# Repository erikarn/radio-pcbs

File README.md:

# Welcome!

This is Adrian's playpen for learning and building little radio PCB projects.

All of these projects are licenced under CC BY-SA 2.0 (https://creativecommons.org/licenses/by-sa/2.0/).
Please contact me if you have any commercial desires but don't wish to
share your designs.

Thanks!

-Adrian Chadd
(KK6VQK)

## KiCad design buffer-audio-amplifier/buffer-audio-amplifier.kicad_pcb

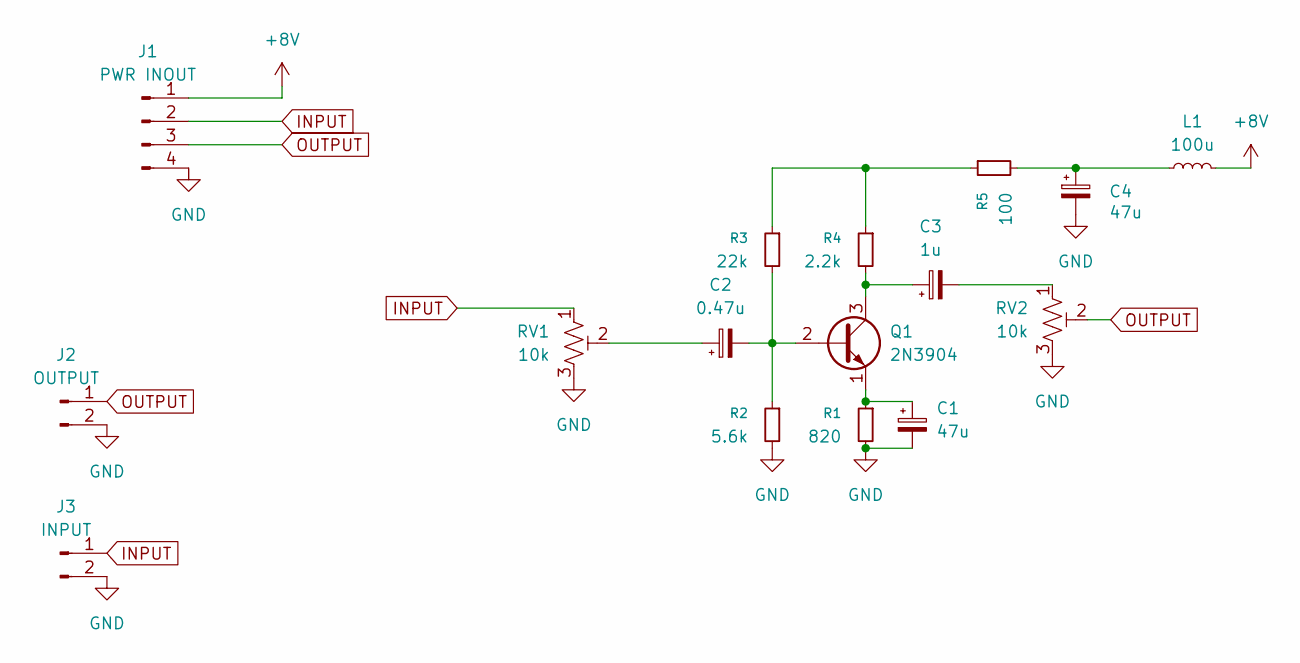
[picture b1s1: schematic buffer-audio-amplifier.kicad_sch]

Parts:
C1, C4: 47u; CP_Radial_D6.3mm_P2.50mm
C2: 0.47u; CP_Radial_D6.3mm_P2.50mm
C3: 1u; CP_Radial_D6.3mm_P2.50mm
J1: PWR INOUT; PinHeader_1x04_P2.54mm_Vertical
J2: OUTPUT; PinHeader_1x02_P2.54mm_Vertical
J3: INPUT; PinHeader_1x02_P2.54mm_Vertical
L1: 100u; L_Axial_L5.3mm_D2.2mm_P7.62mm_Horizontal_Vishay_IM-1
Q1: 2N3904; TO-92_Inline
R1: 820; R_Axial_DIN0204_L3.6mm_D1.6mm_P5.08mm_Horizontal
R2: 5.6k; R_Axial_DIN0204_L3.6mm_D1.6mm_P5.08mm_Horizontal
R3: 22k; R_Axial_DIN0204_L3.6mm_D1.6mm_P5.08mm_Horizontal
R4: 2.2k; R_Axial_DIN0204_L3.6mm_D1.6mm_P5.08mm_Horizontal
R5: 100; R_Axial_DIN0207_L6.3mm_D2.5mm_P7.62mm_Horizontal
RV1, RV2: 10k; Potentiometer_Piher_PT-10-V05_Vertical

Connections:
+8V: J1.1, L1.2
GND: C1.2, C4.2, J1.4, J2.2, J3.2, R1.2, R2.2, RV1.3, RV2.3
INPUT: J1.2, J3.1, RV1.1
unnamed: C2.1, RV1.2
unnamed: C3.2, RV2.1
unnamed: C4.1, L1.1, R5.2
unnamed: C2.2, Q1.2 (B), R2.1, R3.2
unnamed: C3.1, Q1.3 (C), R4.2
unnamed: C1.1, Q1.1 (E), R1.1
unnamed: R3.1, R4.1, R5.1
OUTPUT: J1.3, J2.1, RV2.2

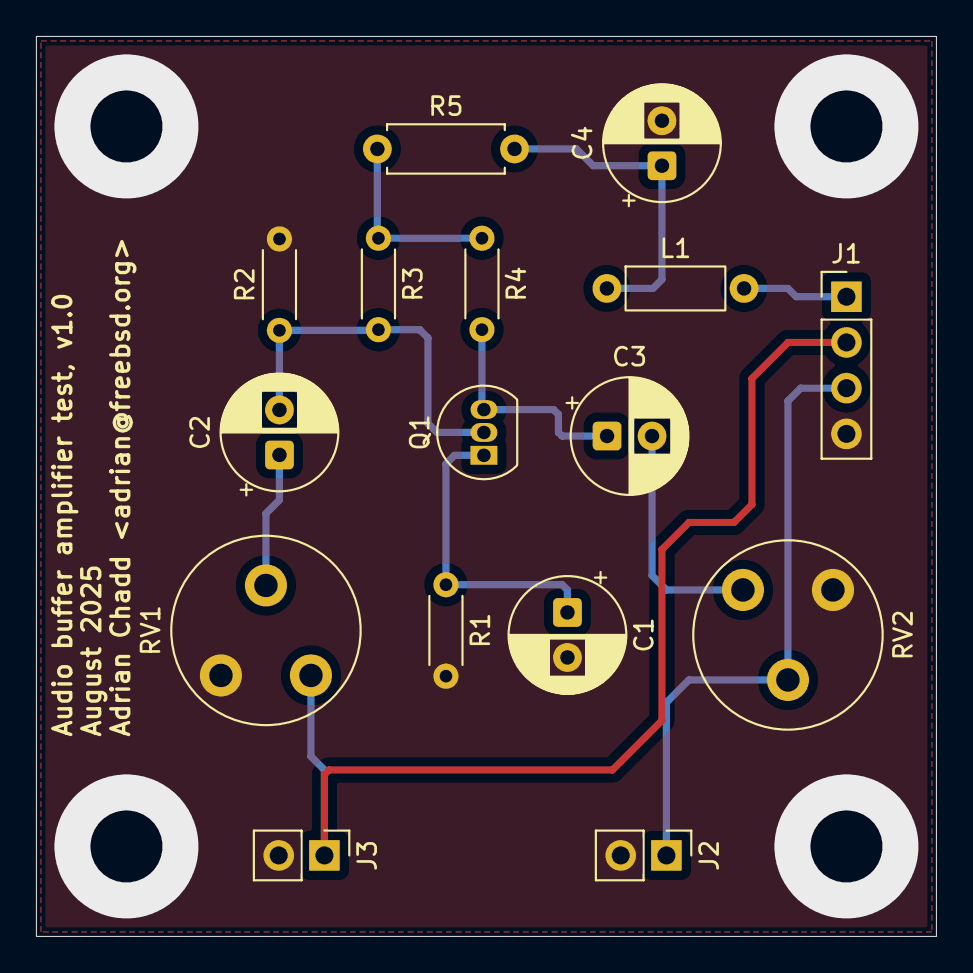
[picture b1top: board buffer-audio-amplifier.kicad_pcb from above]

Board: 2 copper layers, 50.0 x 50.0 mm, 16 parts (0 on the bottom side), 11 nets.

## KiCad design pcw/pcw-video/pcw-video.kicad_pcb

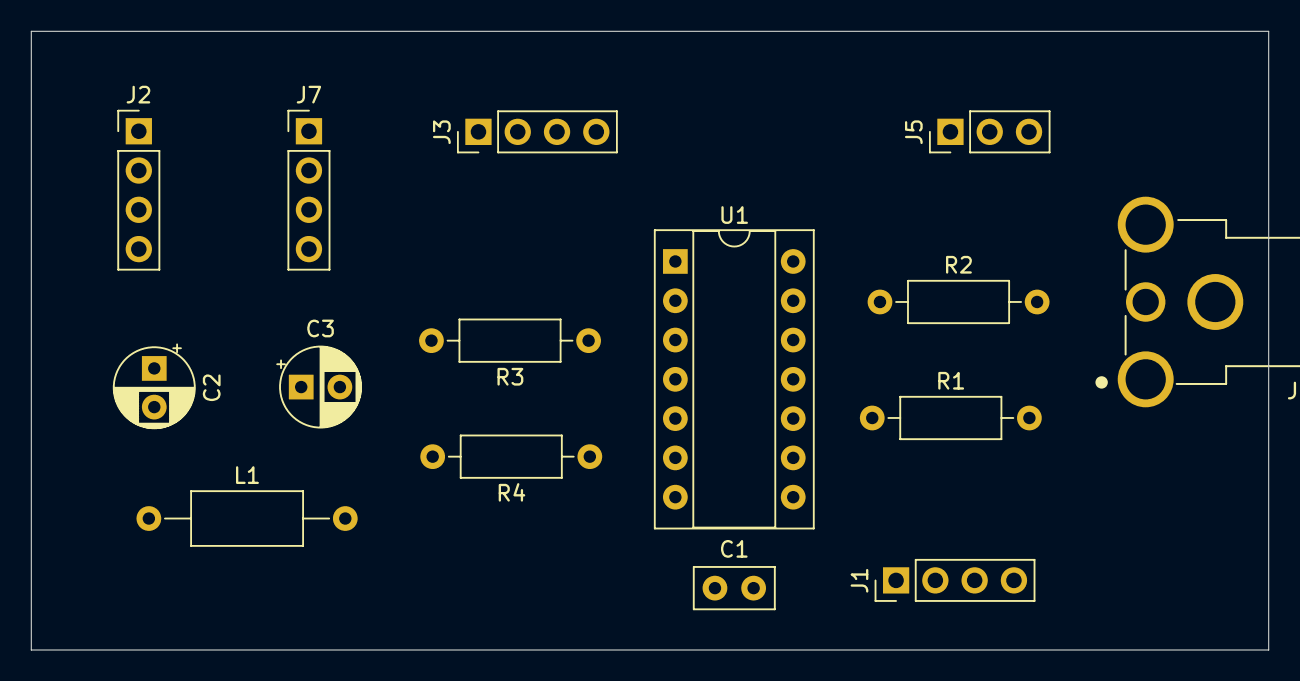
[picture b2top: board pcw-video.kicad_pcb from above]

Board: 2 copper layers, 80.0 x 40.0 mm, 15 parts (0 on the bottom side), 13 nets, no tracks yet.

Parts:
C1: 0.1uF; C_Disc_D5.0mm_W2.5mm_P2.50mm
C2, C3: 1uF; CP_Radial_D5.0mm_P2.50mm
J1: video in; PinHeader_1x04_P2.54mm_Vertical
J2: keyboard in; PinHeader_1x04_P2.54mm_Vertical
J3: video out; PinHeader_1x04_P2.54mm_Vertical
J4: composite out; CUI_RCJ-017
J5: video config; PinHeader_1x03_P2.54mm_Vertical
J7: keyboard out; PinHeader_1x04_P2.54mm_Vertical
L1: 100uH; L_Axial_L7.0mm_D3.3mm_P12.70mm_Horizontal_Fastron_MICC
R1, R2: 5.6k; R_Axial_DIN0207_L6.3mm_D2.5mm_P10.16mm_Horizontal
R3: 470; R_Axial_DIN0207_L6.3mm_D2.5mm_P10.16mm_Horizontal
R4: 1k; R_Axial_DIN0207_L6.3mm_D2.5mm_P10.16mm_Horizontal
U1: 74HC00; CERDIP-14_W7.62mm_SideBrazed_Socket

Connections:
5V_IN: C2.1, J2.2, L1.1
+5V: C1.1, C3.1, J5.1, J7.2, L1.2, U1.2, U1.5, U1.9, U1.12, U1.14 (VCC)
COMP: R3.2, R4.2
GND: C1.2, C2.2, C3.2, J1.2, J1.4, J2.1, J3.2, J3.4, J4.2 (Ext), J5.3, J7.1, R2.2, U1.7 (GND)
unnamed: U1.1, U1.11
unnamed: U1.4, U1.8
PCW_CLK: J2.4, J7.4
PCW_DAT: J2.3, J7.3
SEL1: J5.2, R1.2
SIN: J1.1, R1.1, U1.10
SOUT: J3.1, R4.1, U1.6
VIN: J1.3, R2.1, U1.13
VOUT: J3.3, R3.1, U1.3

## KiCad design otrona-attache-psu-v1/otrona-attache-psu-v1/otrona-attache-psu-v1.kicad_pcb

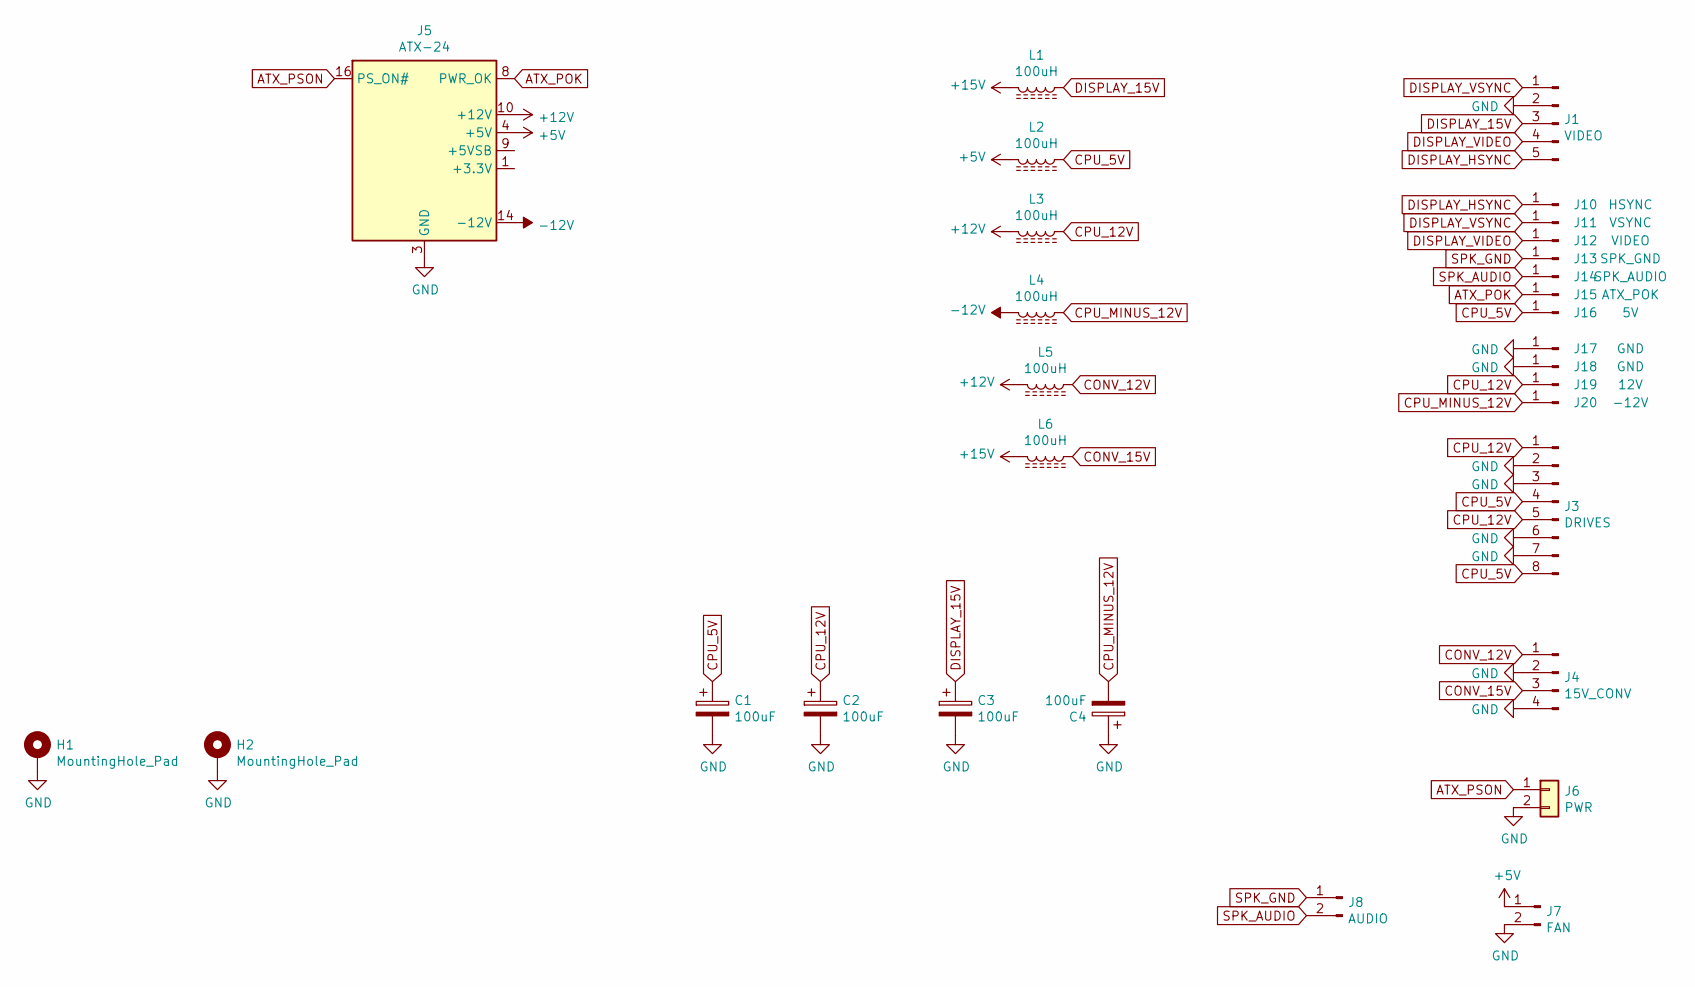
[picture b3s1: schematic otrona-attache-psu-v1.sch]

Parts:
C1, C2, C3, C4: 100uF; CP_Radial_D10.0mm_P5.00mm
H1, H2: MountingHole_Pad; MountingHole_3.5mm
J1: VIDEO; Molex_KK-396_A-41791-0005_1x05_P3.96mm_Vertical
J3: DRIVES; Molex_KK-396_A-41791-0008_1x08_P3.96mm_Vertical
J4: 15V_CONV; PinHeader_1x04_P2.54mm_Horizontal
J5: ATX-24; Molex_Mini-Fit_Jr_5566-24A2_2x12_P4.20mm_Vertical
J6: PWR; PinHeader_1x02_P2.54mm_Horizontal
J7: FAN; PinHeader_1x02_P2.54mm_Horizontal
J8: AUDIO; PinHeader_1x02_P2.54mm_Horizontal
J10: HSYNC; SolderWire-0.75sqmm_1x01_D1.25mm_OD3.5mm
J11: VSYNC; SolderWire-0.75sqmm_1x01_D1.25mm_OD3.5mm
J12: VIDEO; SolderWire-0.75sqmm_1x01_D1.25mm_OD3.5mm
J13: SPK_GND; SolderWire-0.75sqmm_1x01_D1.25mm_OD3.5mm
J14: SPK_AUDIO; SolderWire-0.75sqmm_1x01_D1.25mm_OD3.5mm
J15: ATX_POK; SolderWire-0.75sqmm_1x01_D1.25mm_OD3.5mm
J16: 5V; SolderWire-0.75sqmm_1x01_D1.25mm_OD3.5mm
J17, J18: GND; SolderWire-0.75sqmm_1x01_D1.25mm_OD3.5mm
J19: 12V; SolderWire-0.75sqmm_1x01_D1.25mm_OD3.5mm
J20: -12V; SolderWire-0.75sqmm_1x01_D1.25mm_OD3.5mm
L1, L2, L3, L4, L5, L6: 100uH; L_Axial_L11.0mm_D4.5mm_P15.24mm_Horizontal_Fastron_MECC

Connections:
+5V: J5.4 (+5V), J5.6 (+5V), J5.21 (+5V), J5.22 (+5V), J5.23 (+5V), J7.1, L2.2
+12V: J5.10 (+12V), J5.11 (+12V), L3.2, L5.2
+15V: L1.2, L6.2
-12V: J5.14 (-12V), L4.2
ATX_POK: J5.8 (PWR_OK), J15.1
ATX_PSON: J5.16 (PS_ON#), J6.1
CONV_12V: J4.1, L5.1
CONV_15V: J4.3, L6.1
CPU_5V: C1.1, J3.4, J3.8, J16.1, L2.1
CPU_12V: C2.1, J3.1, J3.5, J19.1, L3.1
CPU_MINUS_12V: C4.2, J20.1, L4.1
DISPLAY_15V: C3.1, J1.3, L1.1
DISPLAY_HSYNC: J1.5, J10.1
DISPLAY_VIDEO: J1.4, J12.1
DISPLAY_VSYNC: J1.1, J11.1
GND: C1.2, C2.2, C3.2, C4.1, H1.1, H2.1, J1.2, J3.2, J3.3, J3.6, J3.7, J4.2, J4.4, J5.3 (GND), J5.5 (GND), J5.7 (GND), J5.15 (GND), J5.17 (GND), J5.18 (GND), J5.19 (GND), J5.24 (GND), J6.2, J7.2, J17.1, J18.1
unnamed: J5.1 (+3.3V), J5.2 (+3.3V), J5.12 (+3.3V), J5.13 (+3.3V)
SPK_AUDIO: J8.2, J14.1
SPK_GND: J8.1, J13.1

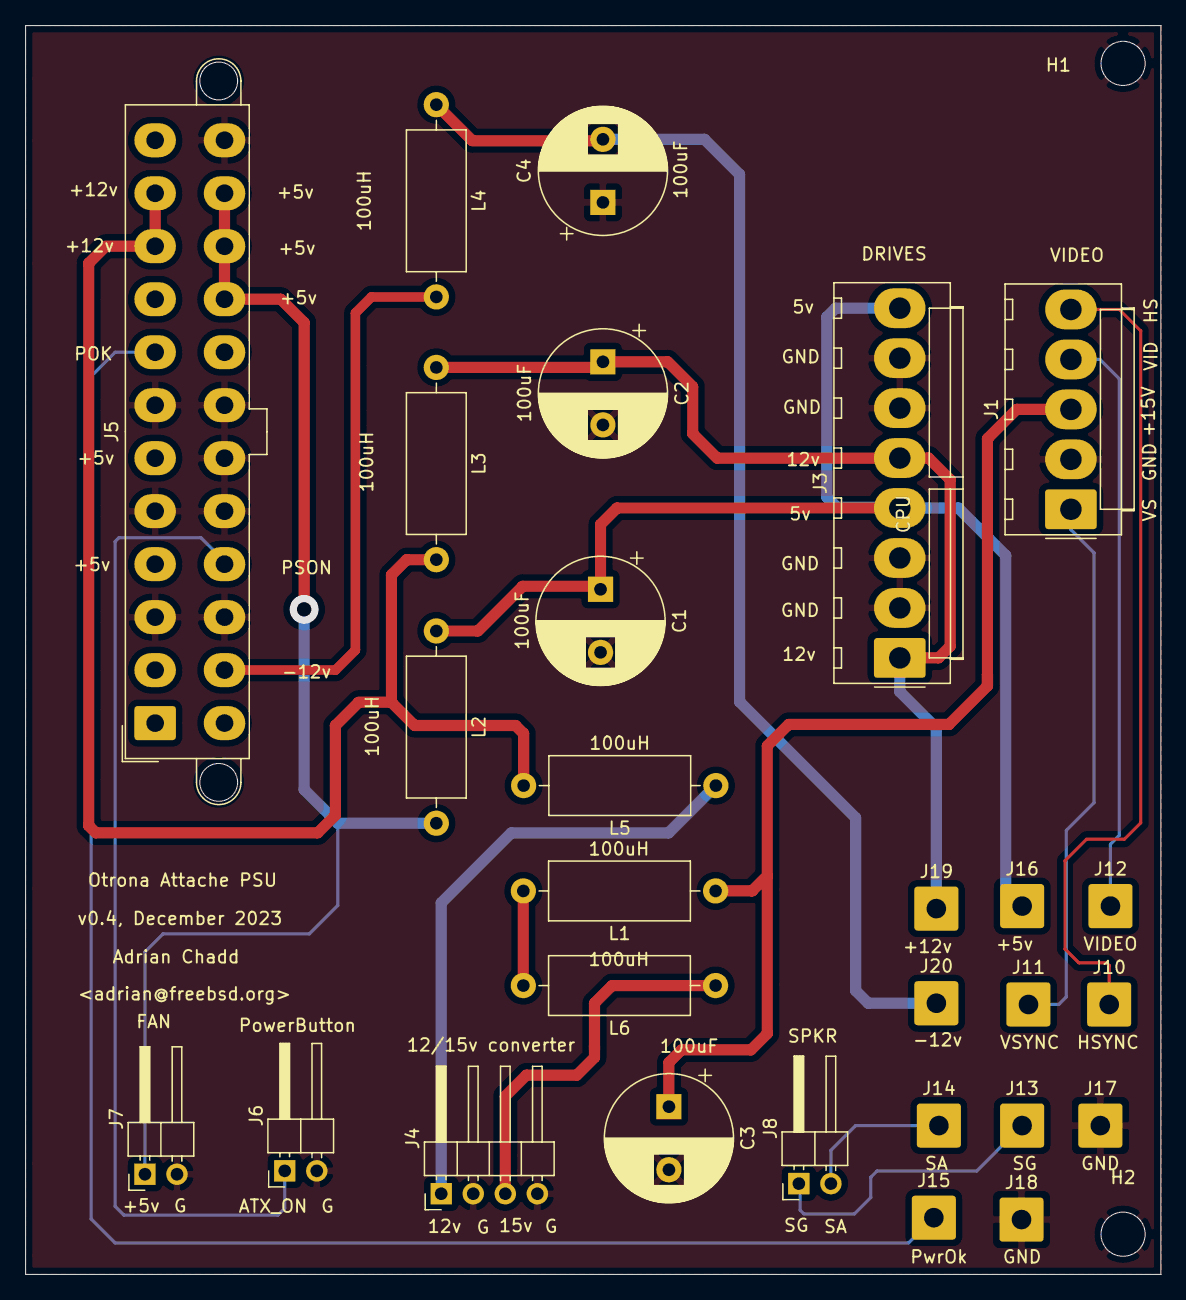
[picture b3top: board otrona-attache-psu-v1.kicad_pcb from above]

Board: 2 copper layers, 90.0 x 99.0 mm, 30 parts (0 on the bottom side), 19 nets.

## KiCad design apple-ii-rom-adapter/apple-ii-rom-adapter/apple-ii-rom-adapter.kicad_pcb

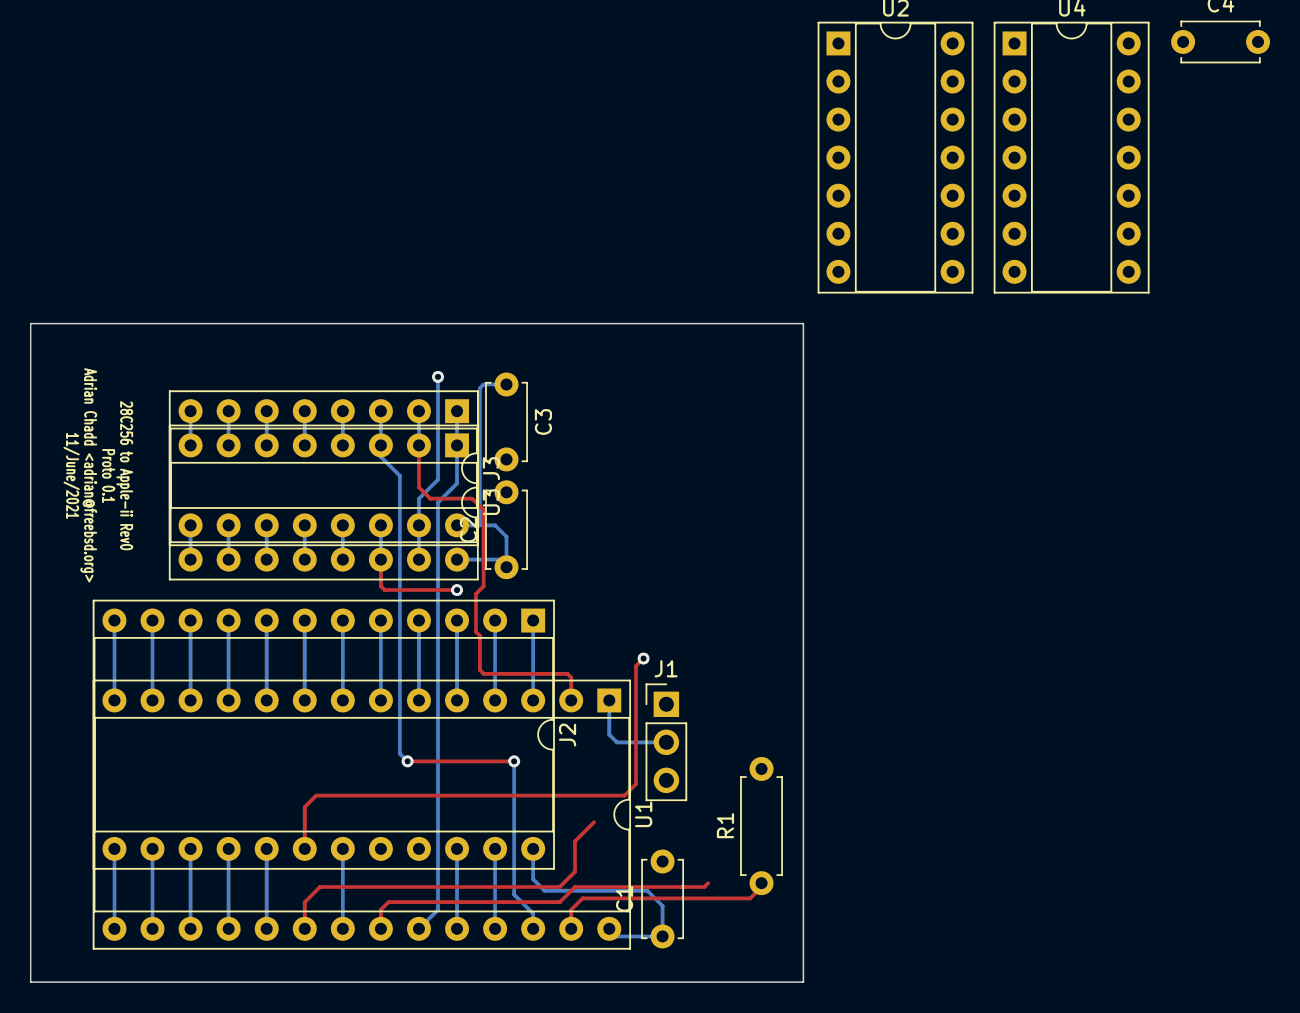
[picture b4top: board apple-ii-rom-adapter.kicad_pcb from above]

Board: 2 copper layers, 51.6 x 43.9 mm, 12 parts (0 on the bottom side), 42 nets.

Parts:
C1, C2, C3, C4: 0.1uF; C_Disc_D5.0mm_W2.5mm_P5.00mm
J1: ROMSEL; PinHeader_1x03_P2.54mm_Vertical
J2: 9316 insert; DIP-24_W15.24mm_Socket
J3: 74LS138 insert; DIP-16_W7.62mm_Socket
R1: 1k; R_Axial_DIN0207_L6.3mm_D2.5mm_P7.62mm_Horizontal
U1: 28C256; DIP-28_W15.24mm_Socket
U2: 74LS20; DIP-14_W7.62mm_Socket
U3: 74LS138; DIP-16_W7.62mm_Socket
U4: 74LS02; DIP-14_W7.62mm_Socket

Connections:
A0: J2.8, U1.10
A1: J2.7, U1.9
A2: J2.6, U1.8
A3: J2.5, U1.7
A4: J2.4, U1.6
A5: J2.3, U1.5
A6: J2.2, U1.4
A7: J2.1, U1.3
A8: J2.23, U1.25
A9: J2.22, U1.24
A10: J2.19, U1.21
A11: J3.1, U1.23, U3.1
A12: J3.2, U1.2, U3.2
A13: J3.3, U1.26, U3.3
A14: J1.2, U1.1
A_CLK0: J3.4, U3.4
A_CLK1: J3.5, U3.5
A_PD: J2.18, U4.2, U4.3
A_SEL_0: J3.15, U3.15
A_SEL_1: J3.14, U3.14
A_SEL_2: J3.13, U2.4, U3.13
A_SEL_3: J3.12, U2.5, U3.12
A_SEL_4: J3.11, U2.9, U3.11
A_SEL_5: J3.10, U2.10, U3.10
A_SEL_6: J3.9, U2.12, U3.9
A_SEL_7: J3.7, U2.13, U3.7
D0: J2.9, U1.11
D1: J2.10, U1.12
D2: J2.11, U1.13
D3: J2.13, U1.15
D4: J2.14, U1.16
D5: J2.15, U1.17
D6: J2.16, U1.18
D7: J2.17, U1.19
E3: J3.6, U3.6
GND: C1.2, C2.2, C3.2, C4.2, J1.3, J2.12, J3.8, U1.14, U2.7, U3.8, U4.7
N_CS: U1.20, U4.4
N_OE: U1.22, U4.1
unnamed: U2.6, U4.5
unnamed: U2.8, U4.6
SOFT_5: J1.1, R1.1, U1.27, U2.1, U2.2, U4.8, U4.9, U4.11, U4.12
VCC: C1.1, C2.1, C3.1, C4.1, J2.24, J3.16, R1.2, U1.28, U2.14, U3.16, U4.14

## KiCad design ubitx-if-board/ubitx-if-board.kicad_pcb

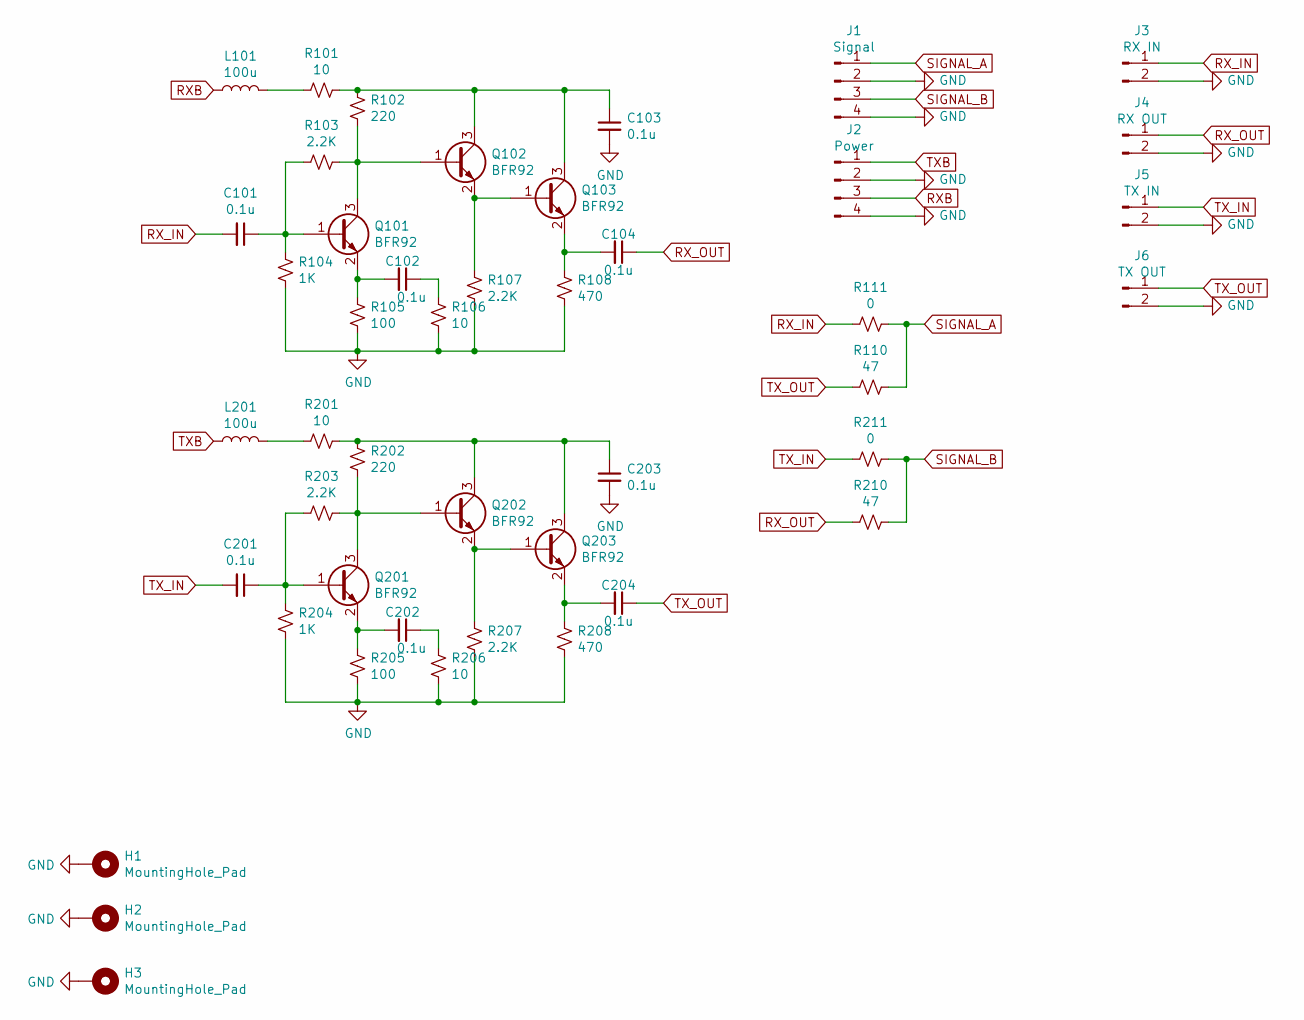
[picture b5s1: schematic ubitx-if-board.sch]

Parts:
C101, C102, C103, C104, C201, C202, C203, C204: 0.1u; C_0603_1608Metric_Pad1.08x0.95mm_HandSolder
H1, H2, H3: MountingHole_Pad; MountingHole_2.2mm_M2_DIN965_Pad_TopBottom
J1: Signal; PinHeader_1x04_P2.54mm_Vertical
J2: Power; PinHeader_1x04_P2.54mm_Vertical
J3: RX IN; PinHeader_1x02_P2.54mm_Vertical
J4: RX OUT; PinHeader_1x02_P2.54mm_Vertical
J5: TX IN; PinHeader_1x02_P2.54mm_Vertical
J6: TX OUT; PinHeader_1x02_P2.54mm_Vertical
L101, L201: 100u; L_1210_3225Metric_Pad1.42x2.65mm_HandSolder
Q101, Q102, Q103, Q201, Q202, Q203: BFR92; SOT-323_SC-70
R101, R106, R201, R206: 10; R_0603_1608Metric_Pad0.98x0.95mm_HandSolder
R102, R202: 220; R_0603_1608Metric_Pad0.98x0.95mm_HandSolder
R103, R107, R203, R207: 2.2K; R_0603_1608Metric_Pad0.98x0.95mm_HandSolder
R104, R204: 1K; R_0603_1608Metric_Pad0.98x0.95mm_HandSolder
R105, R205: 100; R_0603_1608Metric_Pad0.98x0.95mm_HandSolder
R108, R208: 470; R_0603_1608Metric_Pad0.98x0.95mm_HandSolder
R110, R210: 47; R_0603_1608Metric_Pad0.98x0.95mm_HandSolder
R111, R211: 0; R_0603_1608Metric_Pad0.98x0.95mm_HandSolder

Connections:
GND: C103.2, C203.2, H1.1, H2.1, H3.1, J1.2, J1.4, J2.2, J2.4, J3.2, J4.2, J5.2, J6.2, R104.1, R105.2, R106.2, R107.2, R108.2, R204.1, R205.2, R206.2, R207.2, R208.2
unnamed: C101.1, Q101.1 (B), R103.2, R104.2
unnamed: C102.1, R106.1
unnamed: C102.2, Q101.2 (E), R105.1
unnamed: C103.1, Q102.3 (C), Q103.3 (C), R101.1, R102.1
unnamed: C104.2, Q103.2 (E), R108.1
unnamed: C201.1, Q201.1 (B), R203.2, R204.2
unnamed: C202.1, R206.1
unnamed: C202.2, Q201.2 (E), R205.1
unnamed: C203.1, Q202.3 (C), Q203.3 (C), R201.1, R202.1
unnamed: C204.2, Q203.2 (E), R208.1
unnamed: L101.2, R101.2
unnamed: L201.2, R201.2
unnamed: Q101.3 (C), Q102.1 (B), R102.2, R103.1
unnamed: Q102.2 (E), Q103.1 (B), R107.1
unnamed: Q201.3 (C), Q202.1 (B), R202.2, R203.1
unnamed: Q202.2 (E), Q203.1 (B), R207.1
RXB: J2.3, L101.1
RX_IN: C101.2, J3.1, R111.2
RX_OUT: C104.1, J4.1, R210.2
SIGNAL_A: J1.1, R110.1, R111.1
SIGNAL_B: J1.3, R210.1, R211.1
TXB: J2.1, L201.1
TX_IN: C201.2, J5.1, R211.2
TX_OUT: C204.1, J6.1, R110.2

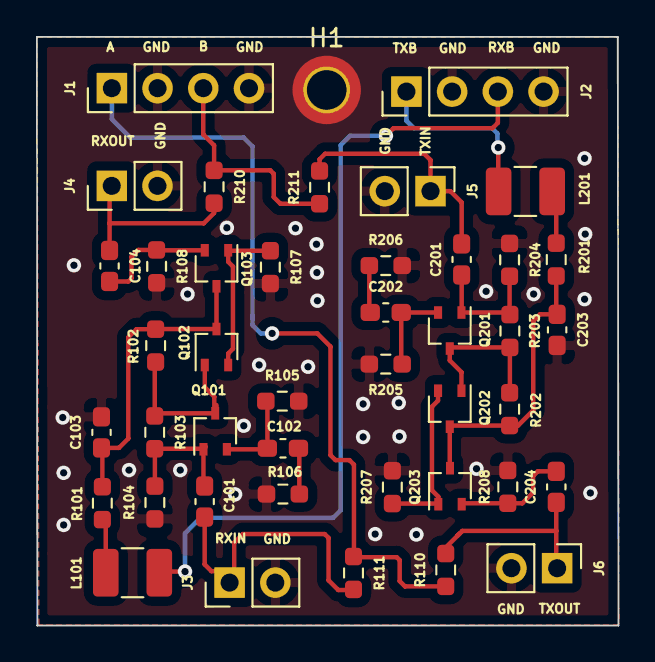
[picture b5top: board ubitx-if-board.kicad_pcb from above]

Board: 2 copper layers, 32.3 x 32.7 mm, 43 parts (0 on the bottom side), 25 nets.

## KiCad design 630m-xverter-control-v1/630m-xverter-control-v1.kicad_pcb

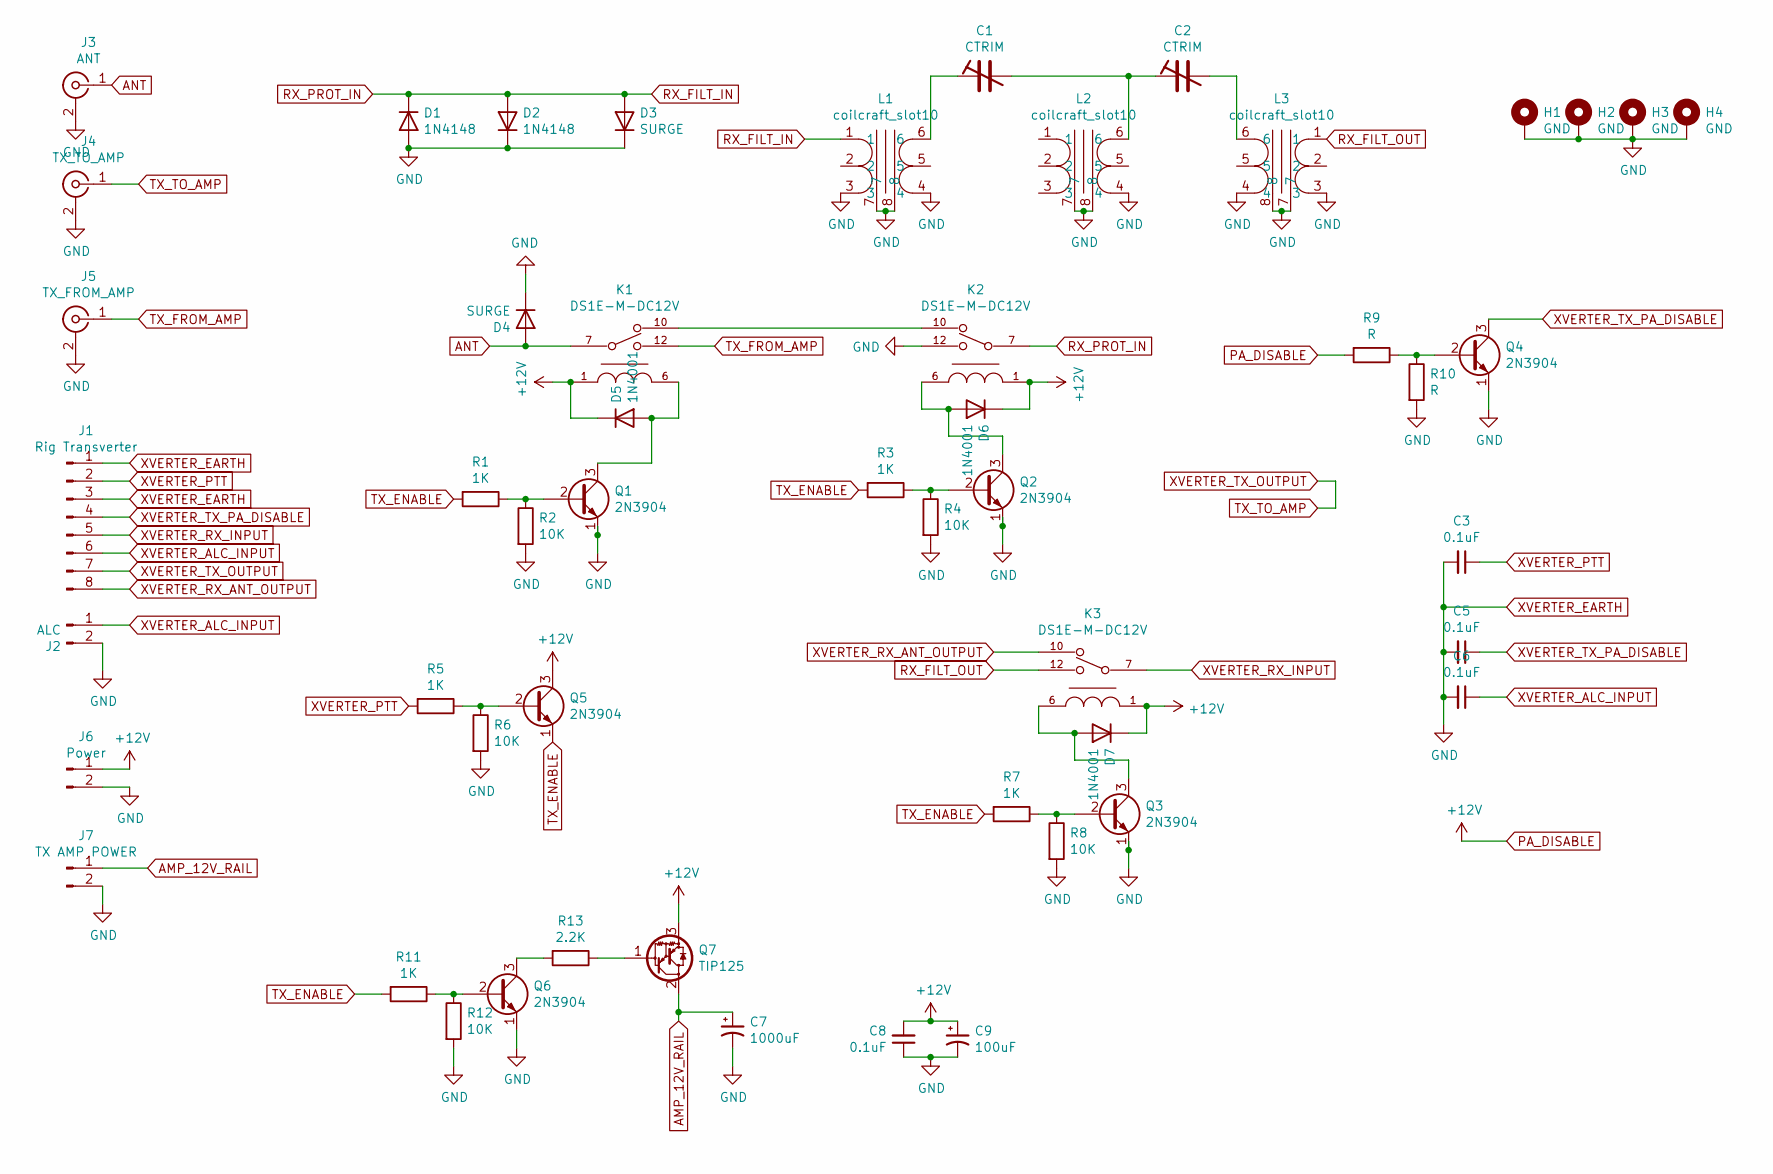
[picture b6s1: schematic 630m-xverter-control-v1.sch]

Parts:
C1, C2: CTRIM; C_Rect_L10.3mm_W5.7mm_P7.50mm_MKS4
C3, C5, C6, C8: 0.1uF; C_Disc_D5.0mm_W2.5mm_P5.00mm
C7: 1000uF; CP_Radial_D10.0mm_P5.00mm
C9: 100uF; CP_Radial_D10.0mm_P2.50mm
D1, D2: 1N4148; D_DO-35_SOD27_P10.16mm_Horizontal
D3, D4: SURGE; D_DO-41_SOD81_P10.16mm_Horizontal
D5, D6, D7: 1N4001; D_DO-41_SOD81_P10.16mm_Horizontal
H1, H2, H3, H4: GND; MountingHole_4.3x6.2mm_M4_Pad_Via
J1: Rig Transverter; PinHeader_1x08_P2.54mm_Vertical
J2: ALC; PinHeader_1x02_P2.54mm_Vertical
J3: ANT; SMA_Amphenol_132134-11_Vertical
J4: TX_TO_AMP; SMA_Amphenol_132134-11_Vertical
J5: TX_FROM_AMP; SMA_Amphenol_132134-11_Vertical
J6: Power; PinHeader_1x02_P2.54mm_Vertical
J7: TX AMP POWER; PinHeader_1x02_P2.54mm_Vertical
K1, K2, K3: DS1E-M-DC12V; DIP-12_W7.62mm; current rating 3A; voltage rating AC 250V; mouser part number 769-DS1E-M-DC12V; digikey description RELAY GEN PURPOSE SPDT 2A 250V
L1, L2, L3: coilcraft_slot10
Q1, Q2, Q3, Q4, Q5, Q6: 2N3904; TO-92_Inline
Q7: TIP125; TO-220-3_Vertical
R1, R3, R5, R7, R11: 1K; R_Axial_DIN0207_L6.3mm_D2.5mm_P7.62mm_Horizontal
R2, R4, R6, R8, R12: 10K; R_Axial_DIN0207_L6.3mm_D2.5mm_P7.62mm_Horizontal
R9, R10: R; R_Axial_DIN0207_L6.3mm_D2.5mm_P7.62mm_Horizontal
R13: 2.2K; R_Axial_DIN0207_L6.3mm_D2.5mm_P10.16mm_Horizontal

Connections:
AMP_12V_RAIL: C7.1, J7.1, Q7.2 (C)
ANT: D4.2 (A), J3.1 (In), K1.7
unnamed: C1.1, L1.6
unnamed: C1.2, C2.1, L2.6
unnamed: C2.2, L3.6
unnamed: D5.2 (A), K1.6, Q1.3 (C)
unnamed: D6.2 (A), K2.6, Q2.3 (C)
unnamed: D7.2 (A), K3.6, Q3.3 (C)
unnamed: K1.10, K2.10
unnamed: Q1.2 (B), R1.1, R2.1
unnamed: Q2.2 (B), R3.1, R4.1
unnamed: Q3.2 (B), R7.1, R8.1
unnamed: Q4.2 (B), R9.1, R10.1
unnamed: Q5.2 (B), R5.1, R6.1
unnamed: Q6.2 (B), R11.1, R12.1
unnamed: Q6.3 (C), R13.2
unnamed: Q7.1 (B), R13.1
PA_DISABLE: C8.2, C9.1, D5.1 (K), D6.1 (K), D7.1 (K), J6.1, K1.1, K2.1, K3.1, Q5.3 (C), Q7.3 (E), R9.2
RX_FILT_IN: D1.1 (K), D2.2 (A), D3.2 (A), K2.7, L1.1
RX_FILT_OUT: K3.12, L3.1
TX_ENABLE: Q5.1 (E), R1.2, R3.2, R7.2, R11.2
TX_FROM_AMP: J5.1 (In), K1.12
TX_TO_AMP: J1.7, J4.1 (In)
XVERTER_ALC_INPUT: C6.1, J1.6, J2.1
XVERTER_EARTH: C3.2, C5.2, C6.2, C7.2, C8.1, C9.2, D1.2 (A), D2.1 (K), D3.1 (K), D4.1 (K), H1.1, H2.1, H3.1, H4.1, J1.1, J1.3, J2.2, J3.2 (Ext), J4.2 (Ext), J5.2 (Ext), J6.2, J7.2, K2.12, L1.3, L1.4, L1.7, L1.8, L2.4, L2.7, L2.8, L3.3, L3.4, L3.7, L3.8, Q1.1 (E), Q2.1 (E), Q3.1 (E), Q4.1 (E), Q6.1 (E), R2.2, R4.2, R6.2, R8.2, R10.2, R12.2
XVERTER_PTT: C3.1, J1.2, R5.2
XVERTER_RX_ANT_OUTPUT: J1.8, K3.10
XVERTER_RX_INPUT: J1.5, K3.7
XVERTER_TX_PA_DISABLE: C5.1, J1.4, Q4.3 (C)

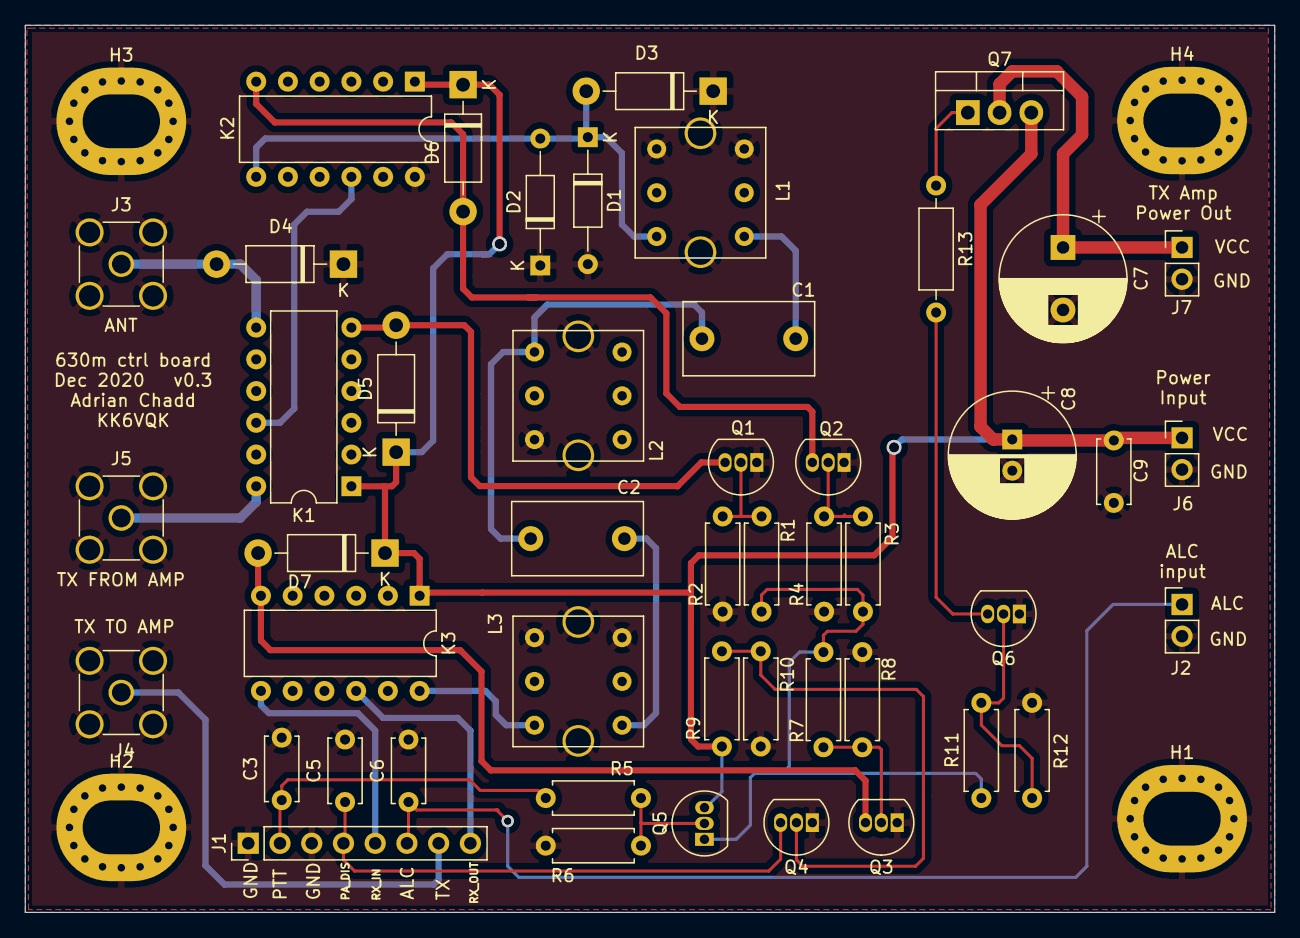
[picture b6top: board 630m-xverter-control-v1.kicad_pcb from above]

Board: 2 copper layers, 100.0 x 71.0 mm, 52 parts (0 on the bottom side), 29 nets.

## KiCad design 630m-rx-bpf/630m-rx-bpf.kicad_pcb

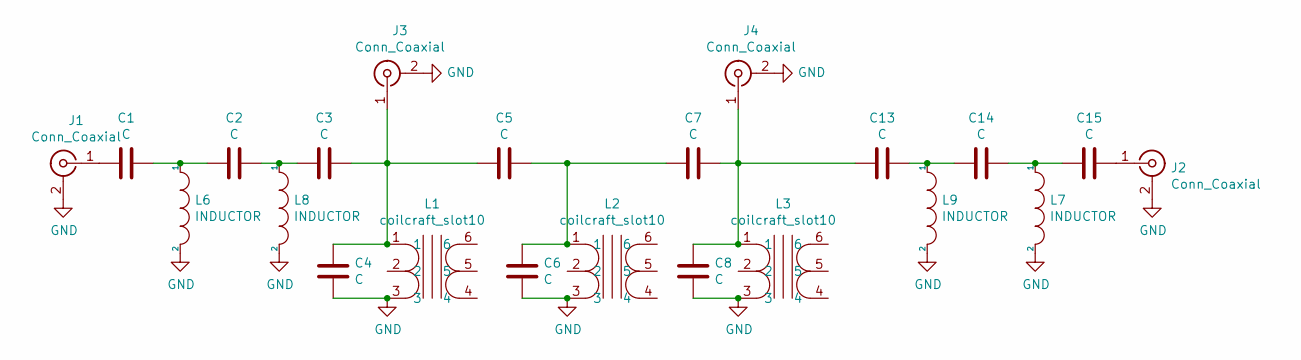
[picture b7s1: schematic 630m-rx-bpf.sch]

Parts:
C1, C2, C3, C4, C5, C6, C7, C8, C13, C14, C15: C; C_Disc_D7.5mm_W4.4mm_P5.00mm
J1, J2, J3, J4: Conn_Coaxial; SMA_Amphenol_132134-14_Vertical
L1, L2, L3: coilcraft_slot10
L6, L7, L8, L9: INDUCTOR; L_Axial_L9.5mm_D4.0mm_P12.70mm_Horizontal_Fastron_SMCC

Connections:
GND: C4.2, C6.2, C8.2, J1.2 (Ext), J2.2 (Ext), J3.2 (Ext), J4.2 (Ext), L1.3, L2.3, L3.3, L6.2, L7.2, L8.2, L9.2
unnamed: C1.1, C2.2, L6.1
unnamed: C1.2, J1.1 (In)
unnamed: C2.1, C3.2, L8.1
unnamed: C3.1, C4.1, C5.2, J3.1 (In), L1.1
unnamed: C5.1, C6.1, C7.2, L2.1
unnamed: C13.1, C14.2, L9.1
unnamed: C7.1, C8.1, C13.2, J4.1 (In), L3.1
unnamed: C14.1, C15.2, L7.1
unnamed: C15.1, J2.1 (In)

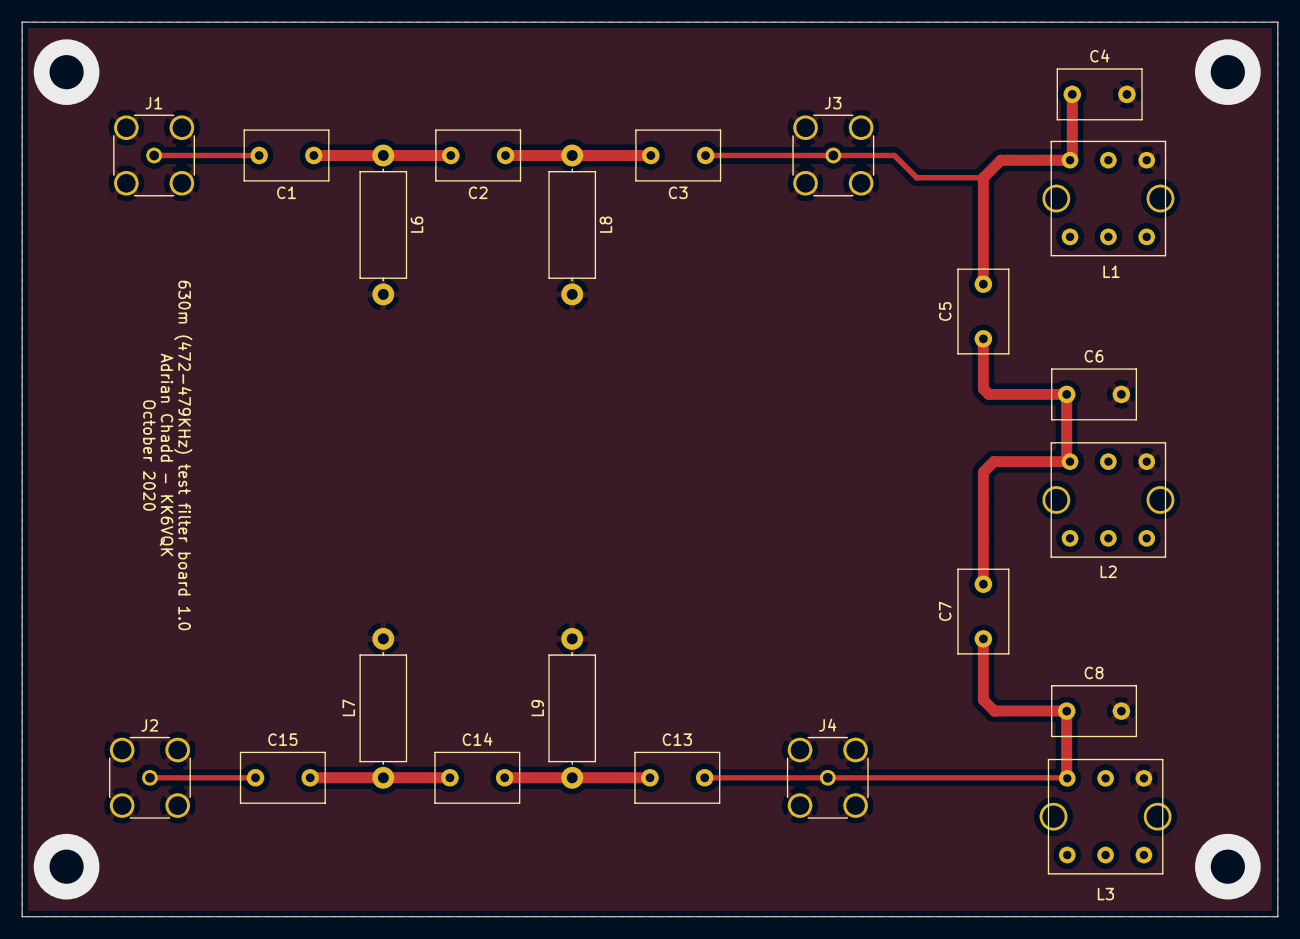
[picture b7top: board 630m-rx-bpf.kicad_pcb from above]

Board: 2 copper layers, 114.8 x 81.8 mm, 22 parts (0 on the bottom side), 10 nets.
